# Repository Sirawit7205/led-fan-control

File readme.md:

# LED Fan Controller

This is an open-source KiCAD design files for a retrofitting controller for cheap rechargeable USB fan with LED lights.

This board is an upgrade (I hope) for the old control board for lead-acid battery that broke down.

## Pictures

## Features

- 1A Charging via USB Type-C port or external 5V power.
- BQ25185DLH Battery charger IC
- BQ29701DSE Battery protection IC with extremely low RDS(on) MOSFET pair
- TPS61088RHL Boost converter from Vbat to 8V motor voltage
- DRV8876PWP Brushed DC Fan driver
- MCU control for fan and led levels.
	
## Revisions

We are currently at Revision 1. Changelog is below:

**Revision 1 (July 2024)**
 - Initial Design
 - Does work, but the Power Path feature on BQ25185DLH is not suitable for high current without cooling. Hits thermal limit in a few minutes.
 - Need to switch to another conventional 1A charger IC.
 - May need to remove DC jack connector as the existing board in the fan is not that good at handling the current.

## What is provided

**The schematics, PCB design, and an interactive BOM is provided.**

Hardware is licensed under `SPDX-License-Identifier: CERN-OHL-S-2.0`

Software is licensed under `SPDX-License-Identifier: GPL` (Firmware is WIP and will be uploaded later.)

Documentation is licensed under `SPDX-License-Identifier: CC-BY-SA-4.0`

## Ordering

You can export gerbers from this project and order the board yourself. You can also use the link below to directly order from Aisler.
https://aisler.net/p/YHUKIBMT

## Credits

 - AMPLF0630 inductor model by Aleksey Zablotskiy: https://grabcad.com/library/amplf-mpc-aspi-etc-smd-power-inductors-1
 - miniSMDC150F fuse model by Karol Novak: https://grabcad.com/library/minismdc150f-1
 - QFN packages model by Jason Traud: https://grabcad.com/library/qfn-packages-1
 - WSON-10 package model by Alex SAR: https://grabcad.com/library/sda10a-rev-a-wson-10-1
 - USB Type-C 6-pin SMD model by ni_ni: https://grabcad.com/library/usb-type-c-smd-6pin-1
 - VQFN-20 package model by Cristian Deenen: https://grabcad.com/library/vqfn-20-3x3mm-1

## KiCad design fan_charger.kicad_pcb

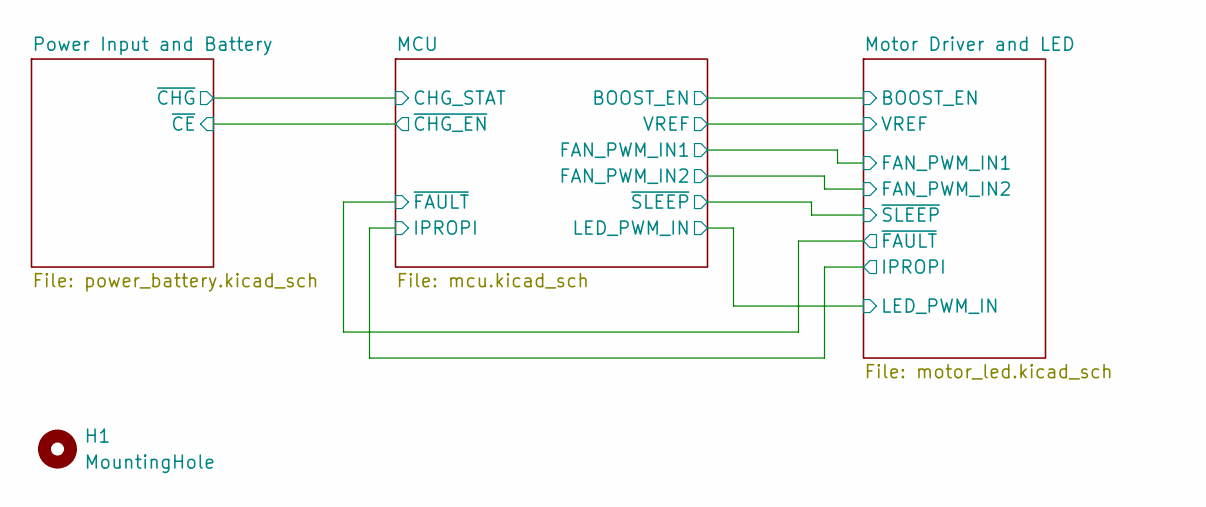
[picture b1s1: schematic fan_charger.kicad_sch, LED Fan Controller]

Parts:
H1: MountingHole; MountingHole_3.2mm_M3

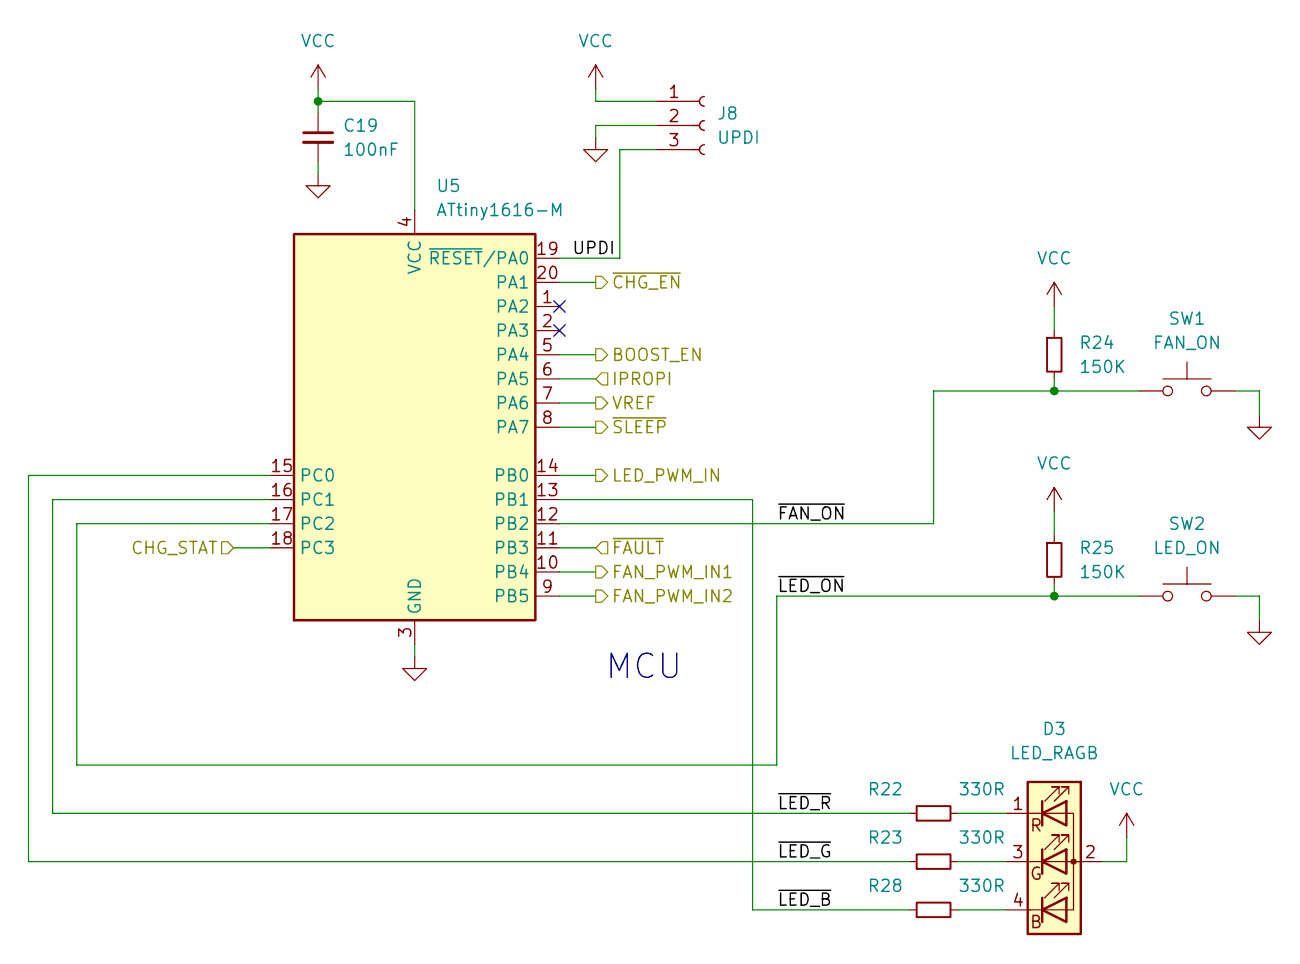
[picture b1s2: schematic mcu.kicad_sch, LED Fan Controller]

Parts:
C19: 100nF; C_0603_1608Metric
D3: LED_RAGB; LED_D5.0mm-4_RGB_Wide_Pins
J8: UPDI; PinHeader_1x03_P2.54mm_Vertical
R22, R23, R28: 330R; R_0603_1608Metric
R24, R25: 150K; R_0603_1608Metric
SW1: FAN_ON; SW_PUSH_6mm
SW2: LED_ON; SW_PUSH_6mm
U5: ATtiny1616-M; VQFN-20-1EP_3x3mm_P0.4mm_EP1.7x1.7mm

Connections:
/MCU/BOOST_EN: U5.5 (PA4); also elsewhere on the board
/MCU/CHG_STAT: U5.18 (PC3); also elsewhere on the board
/MCU/FAN_PWM_IN1: U5.10 (PB4); also elsewhere on the board
/MCU/FAN_PWM_IN2: U5.9 (PB5); also elsewhere on the board
/MCU/IPROPI: U5.6 (PA5); also elsewhere on the board
/MCU/LED_PWM_IN: U5.14 (PB0); also elsewhere on the board
/MCU/UPDI: J8.3, U5.19 (~RESET/PA0)
/MCU/VREF: U5.7 (PA6); also elsewhere on the board
/MCU/~CHG_EN: U5.20 (PA1); also elsewhere on the board
/MCU/~FAN_ON: R24.2, SW1.1, U5.12 (PB2)
/MCU/~FAULT: U5.11 (PB3); also elsewhere on the board
/MCU/~LED_B: R28.1, U5.13 (PB1)
/MCU/~LED_G: R23.1, U5.15 (PC0)
/MCU/~LED_ON: R25.2, SW2.1, U5.17 (PC2)
/MCU/~LED_R: R22.1, U5.16 (PC1)
/MCU/~SLEEP: U5.8 (PA7); also elsewhere on the board
GND: C19.2, J8.2, SW1.2, SW2.2, U5.3 (GND), U5.21 (GND); also elsewhere on the board
unnamed: D3.4 (BK), R28.2
unnamed: D3.3 (GK), R23.2
unnamed: D3.1 (RK), R22.2
VCC: C19.1, D3.2 (A), J8.1, R24.1, R25.1, U5.4 (VCC); also elsewhere on the board

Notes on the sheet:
MCU

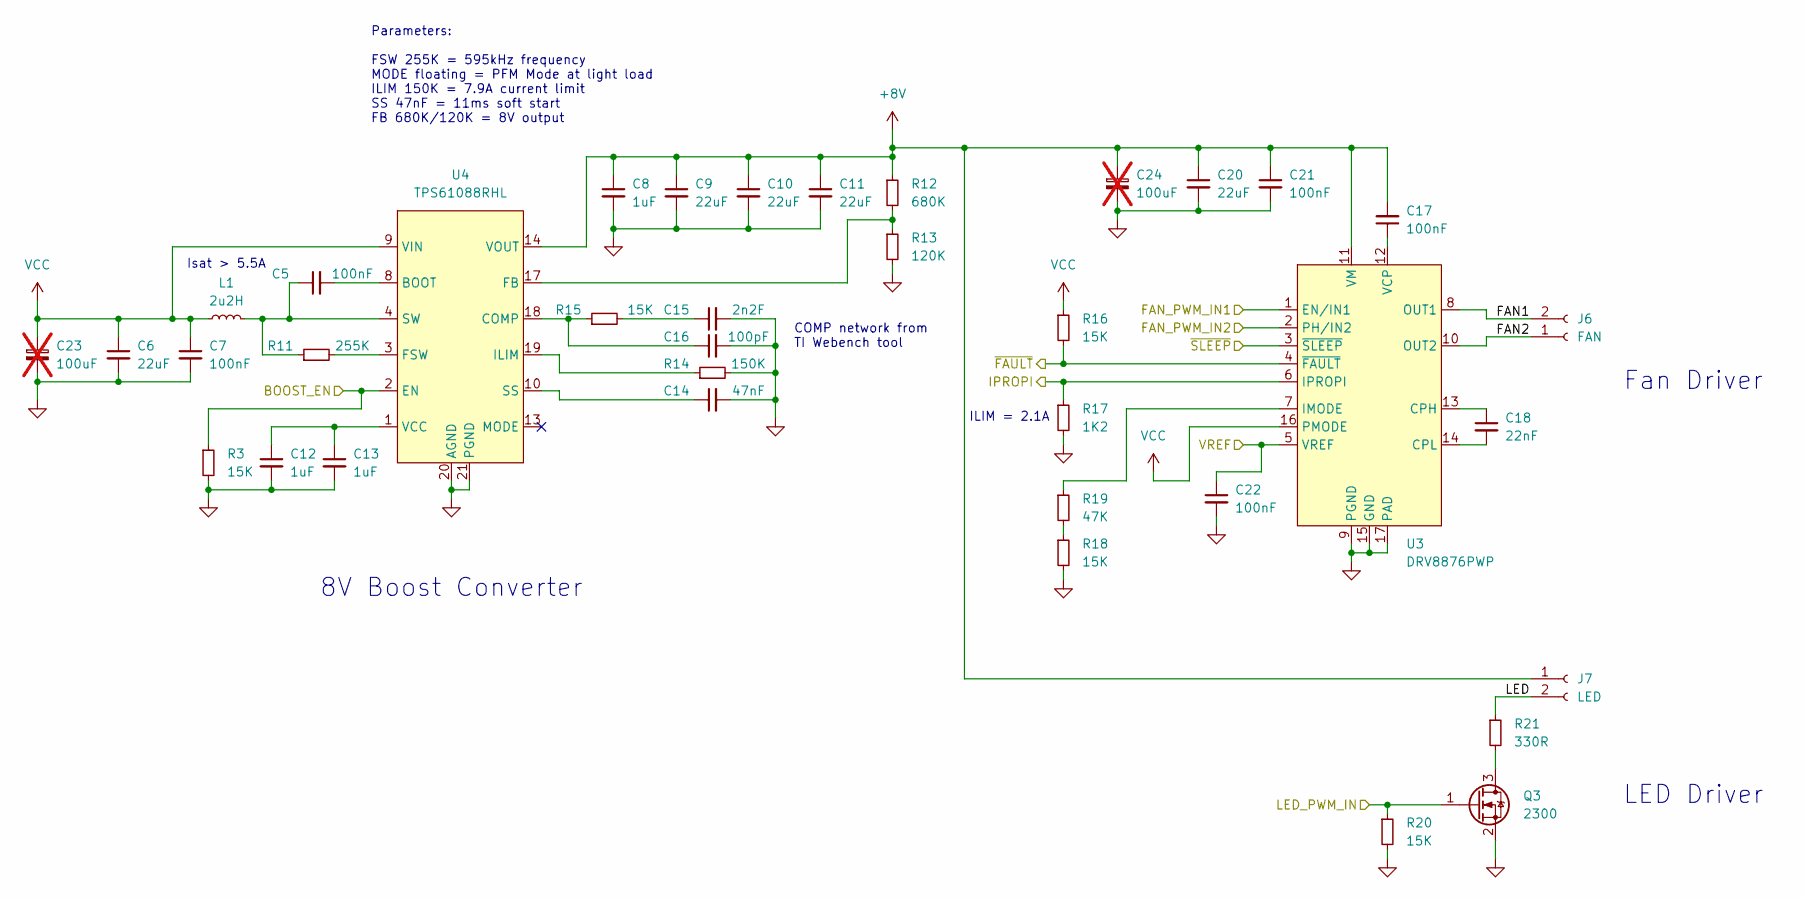
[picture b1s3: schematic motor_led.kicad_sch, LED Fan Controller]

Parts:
C5, C7, C17, C21, C22: 100nF; C_0603_1608Metric
C6, C9, C10, C11, C20: 22uF; C_1210_3225Metric
C8, C12, C13: 1uF; C_0603_1608Metric
C14: 47nF; C_0603_1608Metric
C15: 2n2F; C_0603_1608Metric
C16: 100pF; C_0603_1608Metric
C18: 22nF; C_0603_1608Metric
C23, C24: 100uF; CP_Radial_D6.3mm_P2.50mm; not fitted
J6: FAN; JST_XH_S2B-XH-A_1x02_P2.50mm_Horizontal
J7: LED; JST_XH_S2B-XH-A_1x02_P2.50mm_Horizontal
L1: 2u2H; L_Abracon_ASPI-0630LR
Q3: 2300; SOT-23
R3, R15, R16, R18, R20: 15K; R_0603_1608Metric
R11: 255K; R_0603_1608Metric
R12: 680K; R_0603_1608Metric
R13: 120K; R_0603_1608Metric
R14: 150K; R_0603_1608Metric
R17: 1K2; R_0603_1608Metric
R19: 47K; R_0603_1608Metric
R21: 330R; R_0603_1608Metric
U3: DRV8876PWP; TSSOP-16-1EP_4.4x5mm_P0.65mm
U4: TPS61088RHL; Texas_VQFN-RHL-20

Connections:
+8V: C8.1, C9.1, C10.1, C11.1, C17.2, C20.1, C21.1, C24.1, J7.1, R12.1, U3.11 (VM), U4.14 (VOUT), U4.15 (VOUT), U4.16 (VOUT)
/MCU/BOOST_EN: R3.1, U4.2 (EN); also elsewhere on the board
/MCU/FAN_PWM_IN1: U3.1 (EN/IN1); also elsewhere on the board
/MCU/FAN_PWM_IN2: U3.2 (PH/IN2); also elsewhere on the board
/MCU/IPROPI: R17.1, U3.6 (IPROPI); also elsewhere on the board
/MCU/LED_PWM_IN: Q3.1 (G), R20.1; also elsewhere on the board
/MCU/VREF: C22.1, U3.5 (VREF); also elsewhere on the board
/MCU/~FAULT: R16.2, U3.4 (~FAULT); also elsewhere on the board
/MCU/~SLEEP: U3.3 (~SLEEP); also elsewhere on the board
/Motor Driver and LED/FAN1: J6.2, U3.8 (OUT1)
/Motor Driver and LED/FAN2: J6.1, U3.10 (OUT2)
/Motor Driver and LED/LED: J7.2, R21.1
GND: C6.2, C7.2, C8.2, C9.2, C10.2, C11.2, C12.2, C13.2, C14.2, C15.2, C16.2, C20.2, C21.2, C22.2, C23.2, C24.2, Q3.2 (S), R3.2, R13.2, R14.2, R17.2, R18.2, R20.2, U3.9 (PGND), U3.15 (GND), U3.17 (PAD), U4.20 (AGND), U4.21 (PGND); also elsewhere on the board
unnamed: C5.1, L1.2, R11.1, U4.4 (SW), U4.5 (SW), U4.6 (SW), U4.7 (SW)
unnamed: C15.1, R15.2
unnamed: Q3.3 (D), R21.2
unnamed: R18.1, R19.2
unnamed: C18.1, U3.13 (CPH)
unnamed: C18.2, U3.14 (CPL)
unnamed: R19.1, U3.7 (IMODE)
unnamed: C17.1, U3.12 (VCP)
unnamed: C5.2, U4.8 (BOOT)
unnamed: C16.1, R15.1, U4.18 (COMP)
unnamed: R12.2, R13.1, U4.17 (FB)
unnamed: R11.2, U4.3 (FSW)
unnamed: R14.1, U4.19 (ILIM)
unnamed: C14.1, U4.10 (SS)
unnamed: C12.1, C13.1, U4.1 (VCC)
VCC: C6.1, C7.1, C23.1, L1.1, R16.1, U3.16 (PMODE), U4.9 (VIN); also elsewhere on the board

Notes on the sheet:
Fan Driver
Isat > 5.5A
LED Driver
Parameters: FSW 255K = 595kHz frequency MODE floating = PFM Mode at light load ILIM 150K = 7.9A current limit SS 47nF = 11ms soft start FB 680K/120K = 8V output
ILIM = 2.1A
8V Boost Converter
COMP network from TI Webench tool

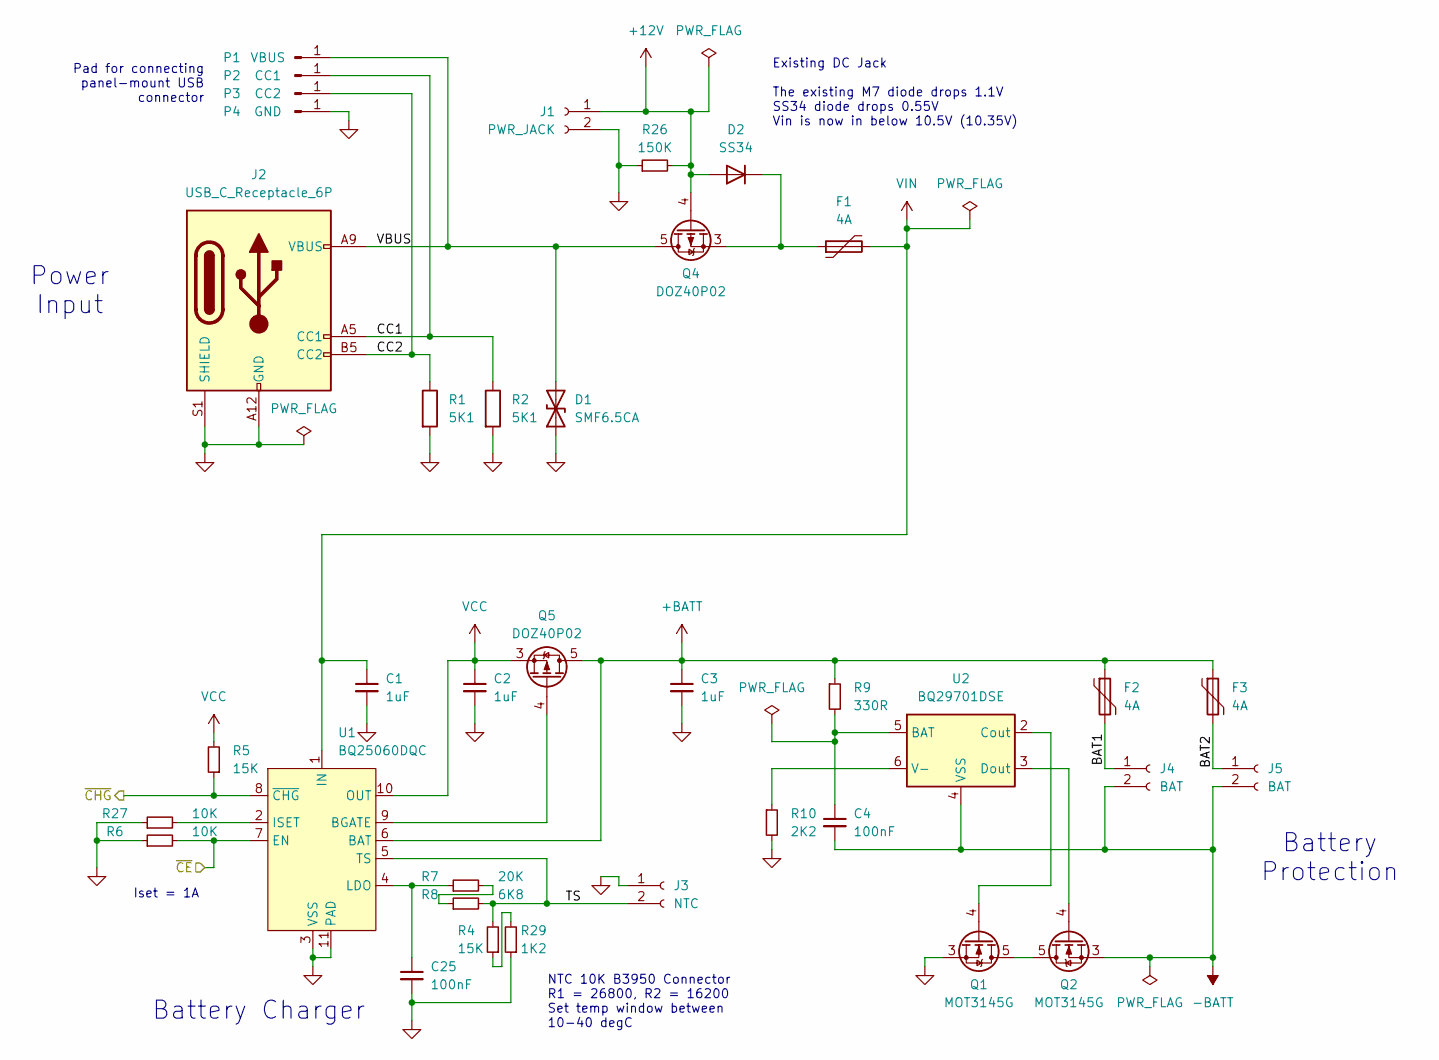
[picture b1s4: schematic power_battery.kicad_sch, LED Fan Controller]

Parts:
C1, C2, C3: 1uF; C_0805_2012Metric
C4, C25: 100nF; C_0603_1608Metric
D1: SMF6.5CA; D_SOD-123F
D2: SS34; D_SMA
F1, F2, F3: 4A; Fuse_1812_4532Metric
J1: PWR_JACK; JST_XH_S2B-XH-A_1x02_P2.50mm_Horizontal
J2: USB_C_Receptacle_6P; USB_C_Receptacle_HRO_TYPE-C-31-M-17
J3: NTC; JST_XH_S2B-XH-A_1x02_P2.50mm_Horizontal
J4, J5: BAT; JST_XH_S2B-XH-A_1x02_P2.50mm_Horizontal
P1: VBUS; TestPoint_THTPad_2.0x2.0mm_Drill1.0mm
P2: CC1; TestPoint_THTPad_2.0x2.0mm_Drill1.0mm
P3: CC2; TestPoint_THTPad_2.0x2.0mm_Drill1.0mm
P4: GND; TestPoint_THTPad_2.0x2.0mm_Drill1.0mm
Q1, Q2: MOT3145G; PQFN-8-EP_6x5mm_P1.27mm_Generic
Q4, Q5: DOZ40P02; VSON-8_3.3x3.3mm_P0.65mm_NexFET
R1, R2: 5K1; R_0603_1608Metric
R4, R5: 15K; R_0603_1608Metric
R6, R27: 10K; R_0603_1608Metric
R7: 20K; R_0603_1608Metric
R8: 6K8; R_0603_1608Metric
R9: 330R; R_0603_1608Metric
R10: 2K2; R_0603_1608Metric
R26: 150K; R_0603_1608Metric
R29: 1K2; R_0603_1608Metric
U1: BQ25060DQC; WSON-10-1EP_2x3mm_P0.5mm_EP0.84x2.4mm
U2: BQ29701DSE; WSON-6_1.5x1.5mm_P0.5mm

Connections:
+12V: D2.2 (A), J1.1, Q4.4 (G), R26.2
+BATT: C3.1, F2.1, F3.1, Q5.5 (D), R9.1, U1.6 (BAT)
-BATT: C4.2, J4.2, J5.2, Q2.1 (S), Q2.2 (S), Q2.3 (S), U2.4 (VSS)
/MCU/CHG_STAT: R5.1, U1.8 (~CHG); also elsewhere on the board
/MCU/~CHG_EN: R6.2, U1.7 (EN); also elsewhere on the board
/Power Input and Battery/BAT1: F2.2, J4.1
/Power Input and Battery/BAT2: F3.2, J5.1
/Power Input and Battery/CC1: J2.A5 (CC1), P2.1, R2.1
/Power Input and Battery/CC2: J2.B5 (CC2), P3.1, R1.1
/Power Input and Battery/TS: J3.2, R4.2, R8.2, U1.5 (TS)
/Power Input and Battery/VBUS: D1.2 (A2), J2.A9 (VBUS), J2.B9 (VBUS), P1.1, Q4.5 (D)
GND: C1.2, C2.2, C3.2, C25.2, D1.1 (A1), J1.2, J2.A12 (GND), J2.B12 (GND), J2.S1 (SHIELD), J3.1, P4.1, Q1.1 (S), Q1.2 (S), Q1.3 (S), R1.2, R2.2, R6.1, R10.2, R26.1, R27.1, R29.1, U1.3 (VSS), U1.11 (PAD); also elsewhere on the board
unnamed: D2.1 (K), F1.1, Q4.1 (S), Q4.2 (S), Q4.3 (S)
unnamed: Q1.5 (D), Q2.5 (D)
unnamed: Q1.4 (G), U2.2 (Cout)
unnamed: Q2.4 (G), U2.3 (Dout)
unnamed: Q5.4 (G), U1.9 (BGATE)
unnamed: R7.2, R8.1
unnamed: R4.1, R29.2
unnamed: R27.2, U1.2 (ISET)
unnamed: C25.1, R7.1, U1.4 (LDO)
unnamed: C4.1, R9.2, U2.5 (BAT)
unnamed: R10.1, U2.6 (V-)
VCC: C2.1, Q5.1 (S), Q5.2 (S), Q5.3 (S), R5.2, U1.10 (OUT); also elsewhere on the board
VIN: C1.1, F1.2, U1.1 (IN)

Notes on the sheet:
Existing DC Jack The existing M7 diode drops 1.1V SS34 diode drops 0.55V Vin is now in below 10.5V (10.35V)
Battery Charger
NTC 10K B3950 Connector R1 = 26800, R2 = 16200 Set temp window between 10-40 degC
Battery Protection
Power Input
Pad for connecting panel-mount USB connector
Iset = 1A

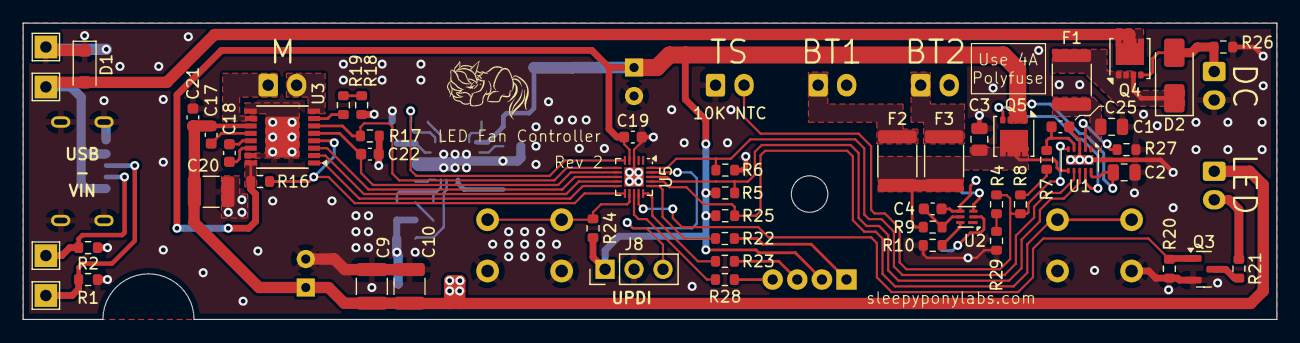
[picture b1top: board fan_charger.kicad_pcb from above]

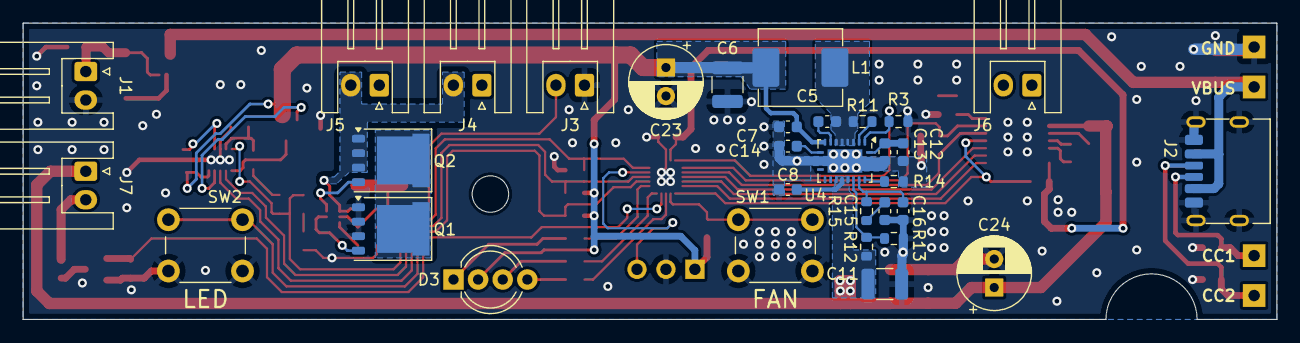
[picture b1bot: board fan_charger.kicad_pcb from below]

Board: 2 copper layers, 110.0 x 26.0 mm, 86 parts (32 on the bottom side), 61 nets.

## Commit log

2024-12-07 Update to rev 2
